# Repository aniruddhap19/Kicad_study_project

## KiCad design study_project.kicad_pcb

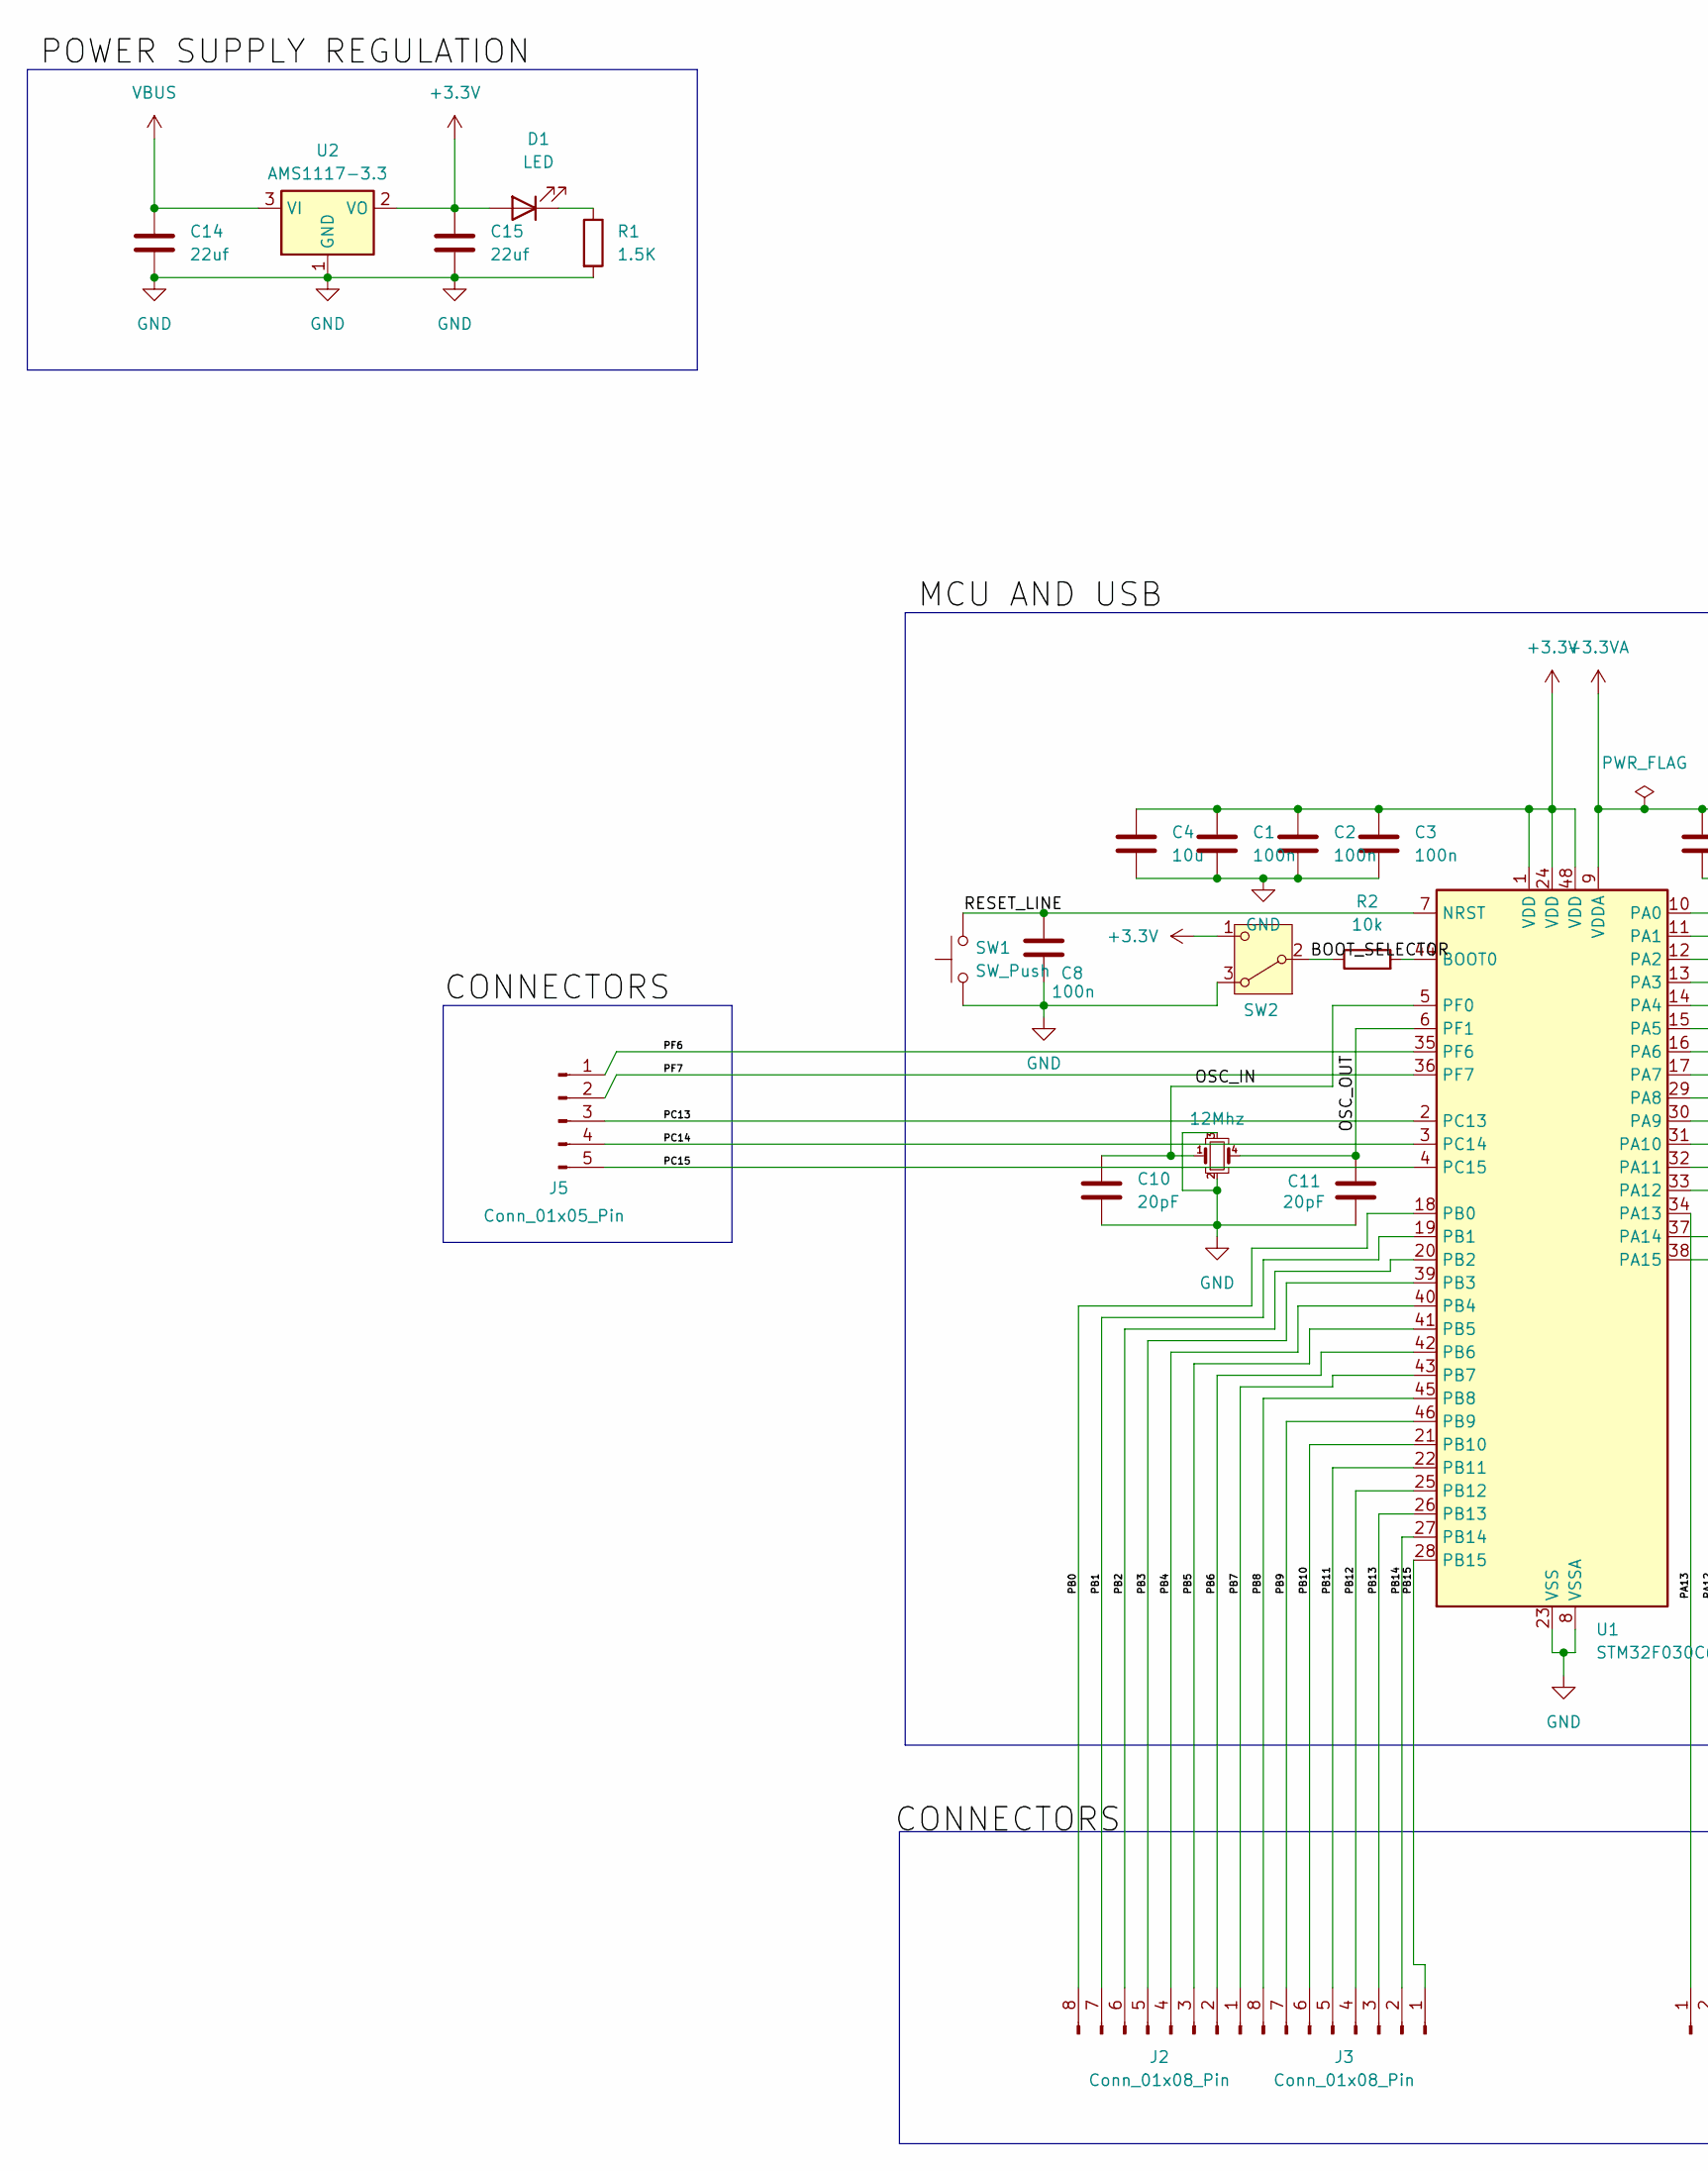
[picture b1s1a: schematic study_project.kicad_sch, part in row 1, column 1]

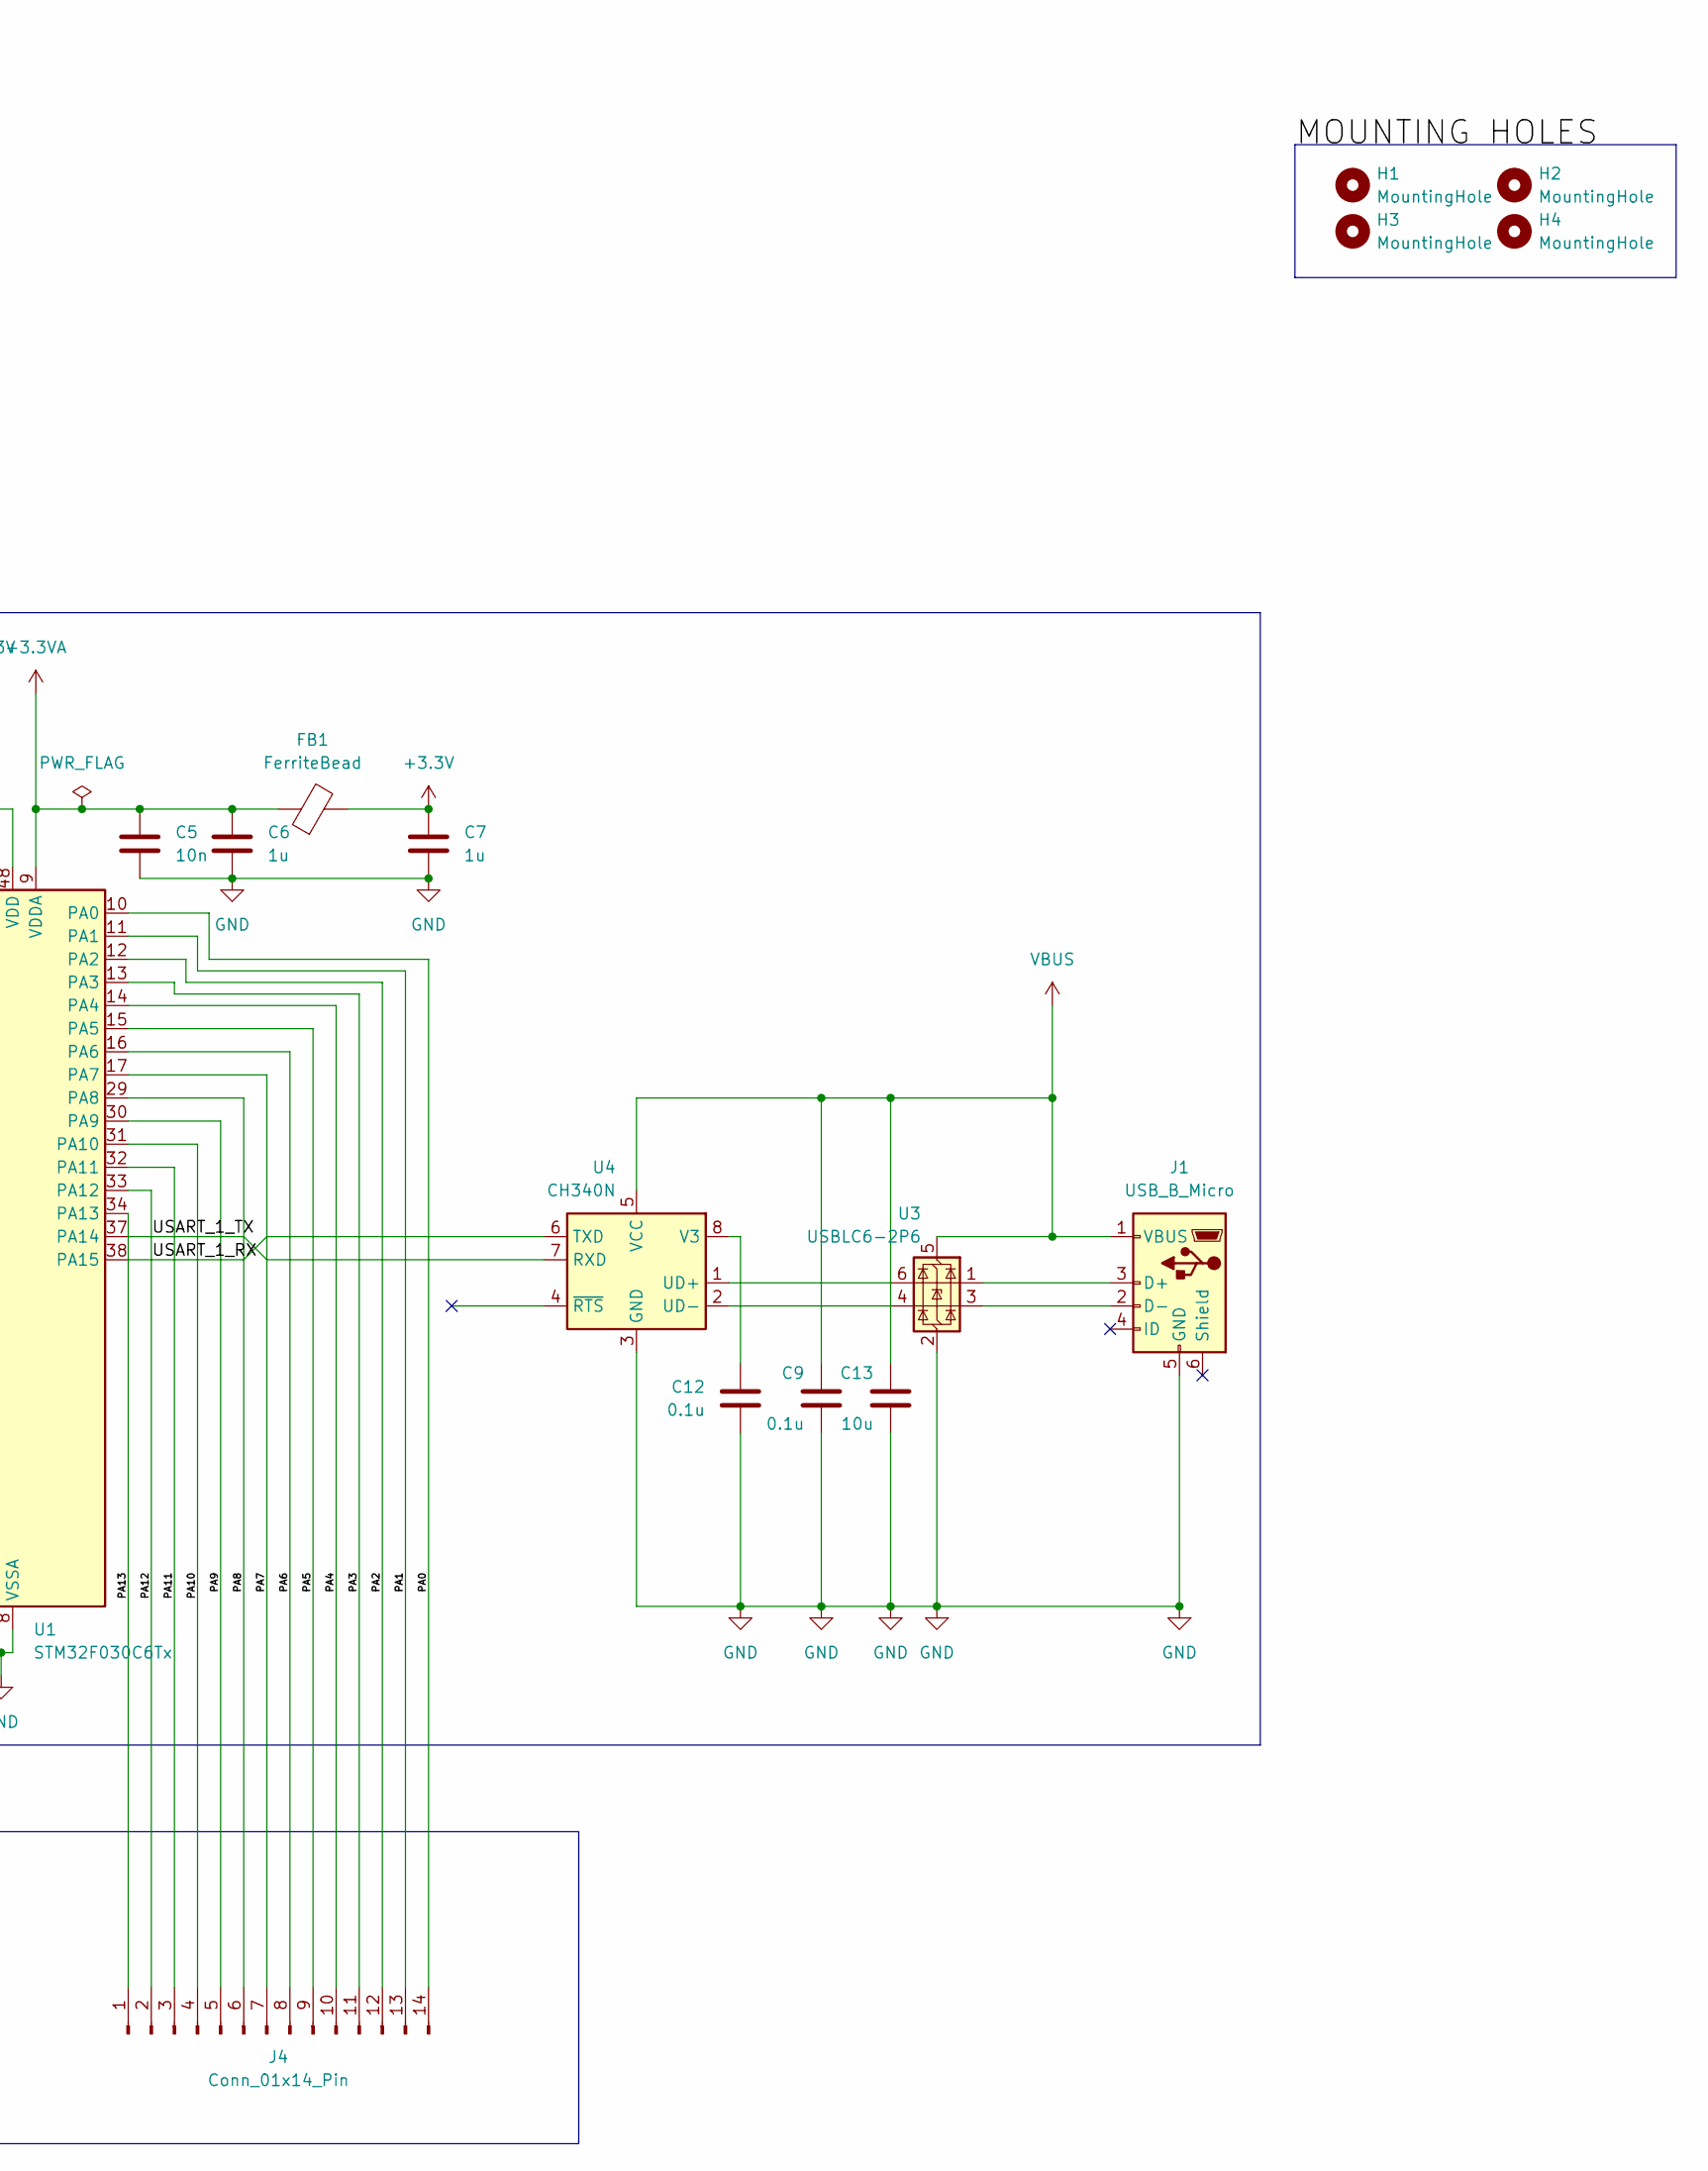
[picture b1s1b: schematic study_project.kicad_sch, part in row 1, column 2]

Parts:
C1, C2, C3, C8: 100n; C_0201_0603Metric_Pad0.64x0.40mm_HandSolder
C4, C13: 10u; C_0402_1005Metric_Pad0.74x0.62mm_HandSolder
C5: 10n; C_0201_0603Metric_Pad0.64x0.40mm_HandSolder
C6, C7: 1u; C_0402_1005Metric_Pad0.74x0.62mm_HandSolder
C9, C12: 0.1u; C_0201_0603Metric_Pad0.64x0.40mm_HandSolder
C10, C11: 20pF; C_0201_0603Metric_Pad0.64x0.40mm_HandSolder
C14, C15: 22uf; C_0402_1005Metric_Pad0.74x0.62mm_HandSolder
D1: LED; LED_0201_0603Metric_Pad0.64x0.40mm_HandSolder
FB1: FerriteBead; L_0402_1005Metric_Pad0.77x0.64mm_HandSolder
H1, H2, H3, H4: MountingHole; MountingHole_2.1mm
J1: USB_B_Micro; USB_Micro-B_Wuerth_629105150521
J2, J3: Conn_01x08_Pin; JST_EH_B8B-EH-A_1x08_P2.50mm_Vertical
J4: Conn_01x14_Pin; JST_EH_B14B-EH-A_1x14_P2.50mm_Vertical
J5: Conn_01x05_Pin; JST_EH_B5B-EH-A_1x05_P2.50mm_Vertical
R1: 1.5K; R_0603_1608Metric_Pad0.98x0.95mm_HandSolder
R2: 10k; R_0201_0603Metric_Pad0.64x0.40mm_HandSolder
SW1: SW_Push; SW_PUSH_6mm
SW2: SW_Nidec_CAS-120A1; SW_SPDT_PCM12
U1: STM32F030C6Tx; LQFP-48_7x7mm_P0.5mm
U2: AMS1117-3.3; SOT-223-3_TabPin2
U3: USBLC6-2P6; SOT-666
U4: CH340N; SOP-8_3.9x4.9mm_P1.27mm
Y1: 12Mhz; Crystal_SMD_2520-4Pin_2.5x2.0mm

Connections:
+3.3V: C1.1, C2.1, C3.1, C4.1, C7.1, C15.1, D1.2 (A), FB1.2, SW2.1 (C), U1.1 (VDD), U1.24 (VDD), U1.48 (VDD), U2.2 (VO)
+3.3VA: C5.1, C6.1, FB1.1, U1.9 (VDDA)
/BOOT_SELECTOR: R2.1, SW2.2 (B)
/OSC_IN: C10.1, U1.5 (PF0), Y1.1
/OSC_OUT: C11.1, U1.6 (PF1), Y1.4
/PA0: J4.14, U1.10 (PA0)
/PA1: J4.13, U1.11 (PA1)
/PA2: J4.12, U1.12 (PA2)
/PA3: J4.11, U1.13 (PA3)
/PA4: J4.10, U1.14 (PA4)
/PA5: J4.9, U1.15 (PA5)
/PA6: J4.8, U1.16 (PA6)
/PA7: J4.7, U1.17 (PA7)
/PA8: J4.6, U1.29 (PA8)
/PA9: J4.5, U1.30 (PA9)
/PA10: J4.4, U1.31 (PA10)
/PA11: J4.3, U1.32 (PA11)
/PA13: J4.1, U1.34 (PA13)
/PB0: J2.8, U1.18 (PB0)
/PB1: J2.7, U1.19 (PB1)
/PB2: J2.6, U1.20 (PB2)
/PB3: J2.5, U1.39 (PB3)
/PB4: J2.4, U1.40 (PB4)
/PB5: J2.3, U1.41 (PB5)
/PB6: J2.2, U1.42 (PB6)
/PB7: J2.1, U1.43 (PB7)
/PB8: J3.8, U1.45 (PB8)
/PB9: J3.7, U1.46 (PB9)
/PB10: J3.6, U1.21 (PB10)
/PB11: J3.5, U1.22 (PB11)
/PB12: J3.4, U1.25 (PB12)
/PB13: J3.3, U1.26 (PB13)
/PB14: J3.2, U1.27 (PB14)
/PB15: J3.1, U1.28 (PB15)
/PC13: J5.3, U1.2 (PC13)
/PC14: J5.4, U1.3 (PC14)
/PC15: J5.5, U1.4 (PC15)
/PF6: J5.1, U1.35 (PF6)
/PF7: J5.2, U1.36 (PF7)
/RESET_LINE: C8.1, SW1.2, U1.7 (NRST)
GND: C1.2, C2.2, C3.2, C4.2, C5.2, C6.2, C7.2, C8.2, C9.2, C10.2, C11.2, C12.2, C13.2, C14.2, C15.2, J1.5 (GND), R1.2, SW1.1, SW2.3 (A), U1.8 (VSSA), U1.23 (VSS), U1.47 (VSS), U2.1 (GND), U3.2 (GND), U4.3 (GND), Y1.2, Y1.3
unnamed: D1.1 (K), R1.1
unnamed: J1.3 (D+), U3.1 (I/O1)
unnamed: J1.2 (D-), U3.3 (I/O2)
unnamed: R2.2, U1.44 (BOOT0)
unnamed: U3.6 (I/O1), U4.1 (UD+)
unnamed: U3.4 (I/O2), U4.2 (UD-)
unnamed: C12.1, U4.8 (V3)
VBUS: C9.1, C13.1, C14.1, J1.1 (VBUS), U2.3 (VI), U3.5 (VBUS), U4.5 (VCC)

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
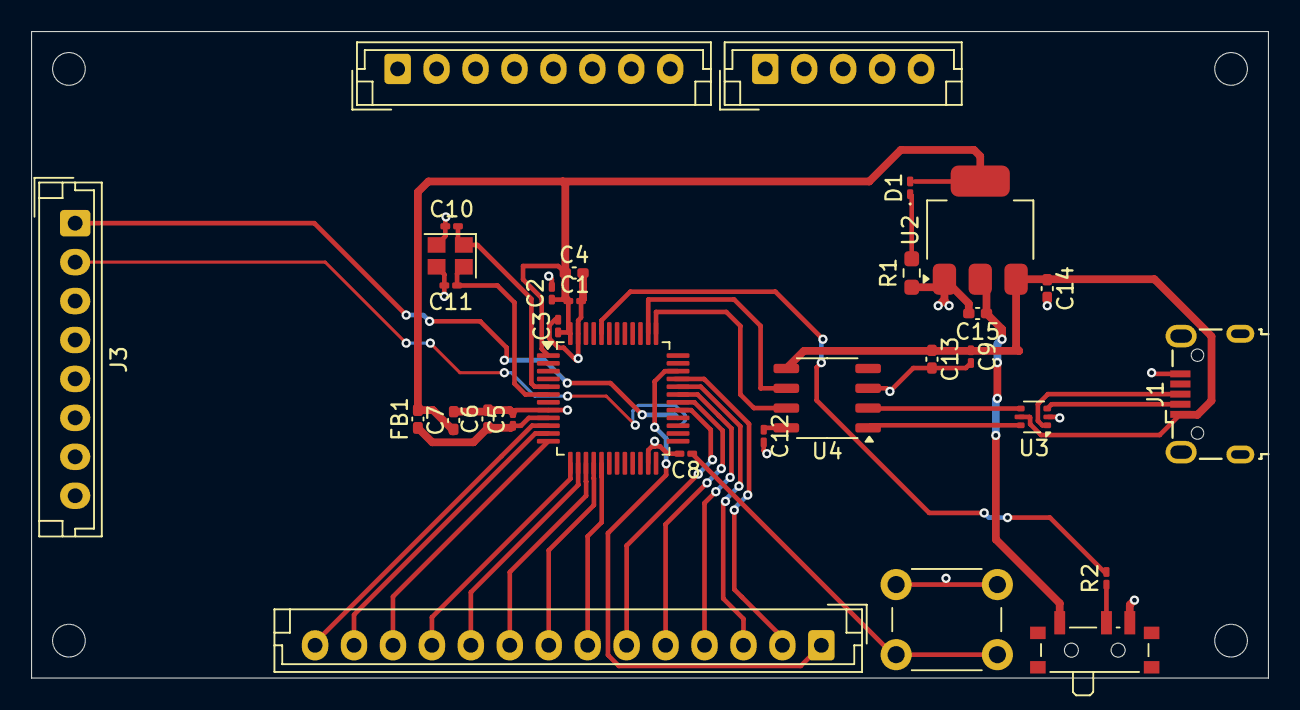
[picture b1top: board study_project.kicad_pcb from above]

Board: 2 copper layers, 79.4 x 41.5 mm, 35 parts (0 on the bottom side), 52 nets.
